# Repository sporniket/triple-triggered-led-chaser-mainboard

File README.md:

# Triple triggered led chaser — Main board

A simple electronic circuit.

Marked as CC0.

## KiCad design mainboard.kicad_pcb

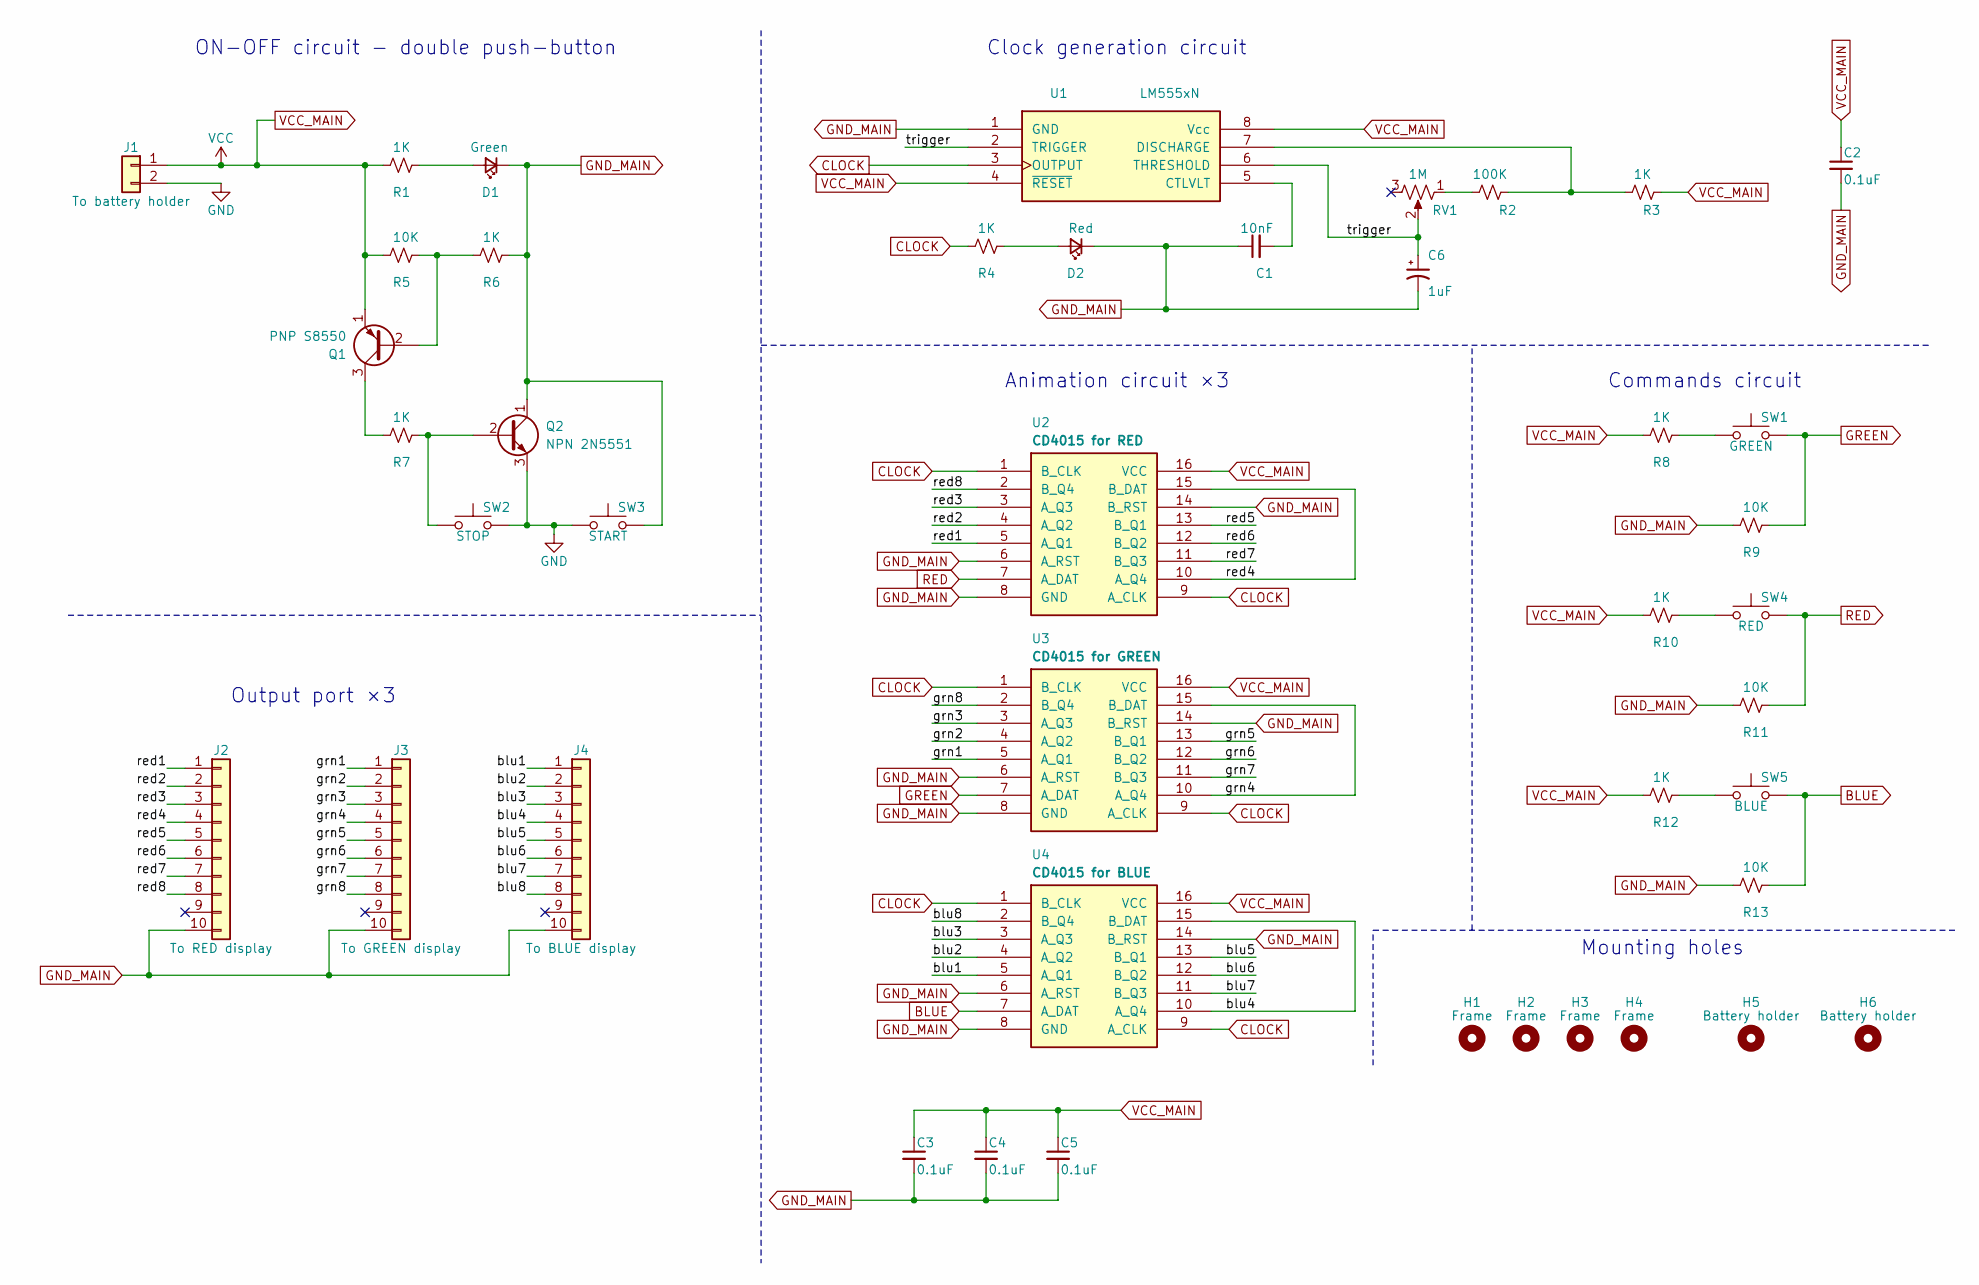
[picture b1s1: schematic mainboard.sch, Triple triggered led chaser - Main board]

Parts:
C1: 10nF; C_Disc_D3.0mm_W1.6mm_P2.50mm
C2, C3, C4, C5: 0.1uF; C_Disc_D3.0mm_W1.6mm_P2.50mm
C6: 1uF; CP_Radial_D4.0mm_P1.50mm
D1: Green; LED_D3.0mm
D2: Red; LED_D3.0mm
H1, H2, H3, H4: Frame; MountingHole_3.2mm_M3_DIN965_Pad
H5, H6: Battery holder; MountingHole_3.2mm_M3_DIN965_Pad
J1: To battery holder; PinHeader_1x02_P2.54mm_Horizontal
J2: To RED display; PinHeader_1x10_P2.54mm_Horizontal
J3: To GREEN display; PinHeader_1x10_P2.54mm_Horizontal
J4: To BLUE display; PinHeader_1x10_P2.54mm_Horizontal
Q1: PNP S8550; TO-92
Q2: NPN 2N5551; TO-92
R1, R3, R4, R6, R7, R8, R10, R12: 1K; R_Axial_DIN0207_L6.3mm_D2.5mm_P10.16mm_Horizontal
R2: 100K; R_Axial_DIN0207_L6.3mm_D2.5mm_P10.16mm_Horizontal
R5, R9, R11, R13: 10K; R_Axial_DIN0207_L6.3mm_D2.5mm_P10.16mm_Horizontal
RV1: 1M; Potentiometer_Piher_PT-6-V_Vertical
SW1: GREEN; SW_PUSH-12mm
SW2: STOP; SW_PUSH-12mm
SW3: START; SW_PUSH-12mm
SW4: RED; SW_PUSH-12mm
SW5: BLUE; SW_PUSH-12mm
U1: LM555xN; DIP-8_W7.62mm
U2: CD4015 for RED; DIP-16_W7.62mm_LongPads
U3: CD4015 for GREEN; DIP-16_W7.62mm_LongPads
U4: CD4015 for BLUE; DIP-16_W7.62mm_LongPads

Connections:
/blu1: J4.1, U4.5 (A_Q1)
/blu2: J4.2, U4.4 (A_Q2)
/blu3: J4.3, U4.3 (A_Q3)
/blu4: J4.4, U4.10 (A_Q4), U4.15 (B_DAT)
/blu5: J4.5, U4.13 (B_Q1)
/blu6: J4.6, U4.12 (B_Q2)
/blu7: J4.7, U4.11 (B_Q3)
/blu8: J4.8, U4.2 (B_Q4)
/grn1: J3.1, U3.5 (A_Q1)
/grn2: J3.2, U3.4 (A_Q2)
/grn3: J3.3, U3.3 (A_Q3)
/grn4: J3.4, U3.10 (A_Q4), U3.15 (B_DAT)
/grn5: J3.5, U3.13 (B_Q1)
/grn6: J3.6, U3.12 (B_Q2)
/grn7: J3.7, U3.11 (B_Q3)
/grn8: J3.8, U3.2 (B_Q4)
/red1: J2.1, U2.5 (A_Q1)
/red2: J2.2, U2.4 (A_Q2)
/red3: J2.3, U2.3 (A_Q3)
/red4: J2.4, U2.10 (A_Q4), U2.15 (B_DAT)
/red5: J2.5, U2.13 (B_Q1)
/red6: J2.6, U2.12 (B_Q2)
/red7: J2.7, U2.11 (B_Q3)
/red8: J2.8, U2.2 (B_Q4)
/trigger: C6.1, RV1.2, U1.2 (TRIGGER), U1.6 (THRESHOLD)
BLUE: R13.1, SW5.2, U4.7 (A_DAT)
CLOCK: R4.2, U1.3 (OUTPUT), U2.1 (B_CLK), U2.9 (A_CLK), U3.1 (B_CLK), U3.9 (A_CLK), U4.1 (B_CLK), U4.9 (A_CLK)
GND: J1.2, Q2.3 (E), SW2.2, SW3.1
GND_MAIN: C1.1, C2.2, C3.2, C4.2, C5.2, C6.2, D1.1 (K), D2.1 (K), J2.10, J3.10, J4.10, Q2.1 (C), R6.1, R9.2, R11.2, R13.2, SW3.2, U1.1 (GND), U2.6 (A_RST), U2.8 (GND), U2.14 (B_RST), U3.6 (A_RST), U3.8 (GND), U3.14 (B_RST), U4.6 (A_RST), U4.8 (GND), U4.14 (B_RST)
GREEN: R9.1, SW1.2, U3.7 (A_DAT)
unnamed: C1.2, U1.5 (CTLVLT)
unnamed: D1.2 (A), R1.1
unnamed: D2.2 (A), R4.1
unnamed: Q1.2 (B), R5.1, R6.2
unnamed: Q1.3 (C), R7.2
unnamed: Q2.2 (B), R7.1, SW2.1
unnamed: R2.1, RV1.1
unnamed: R2.2, R3.1, U1.7 (DISCHARGE)
unnamed: R8.1, SW1.1
unnamed: R10.1, SW4.1
unnamed: R12.1, SW5.1
RED: R11.1, SW4.2, U2.7 (A_DAT)
VCC_MAIN: C2.1, C3.1, C4.1, C5.1, J1.1, Q1.1 (E), R1.2, R3.2, R5.2, R8.2, R10.2, R12.2, U1.4 (~RESET~), U1.8 (Vcc), U2.16 (VCC), U3.16 (VCC), U4.16 (VCC)

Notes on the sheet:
ON-OFF circuit - double push-button
Clock generation circuit
Commands circuit
Animation circuit ×3
Output port ×3
Mounting holes

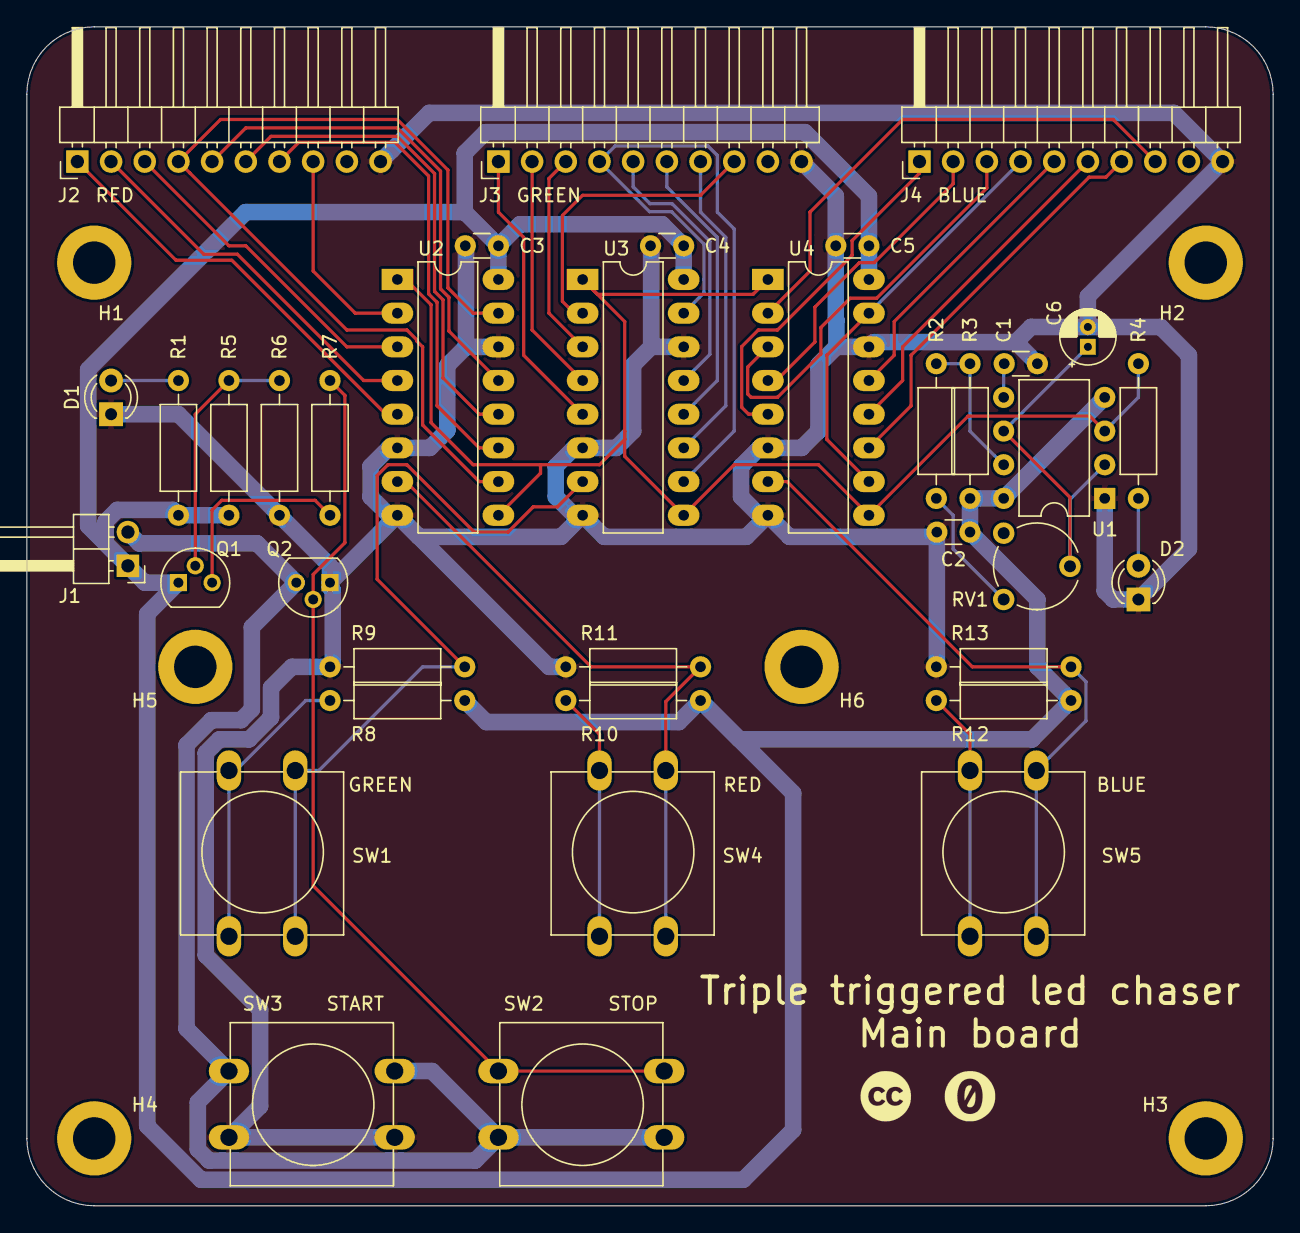
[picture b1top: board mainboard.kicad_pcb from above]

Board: 2 copper layers, 94.0 x 88.9 mm, 43 parts (0 on the bottom side), 43 nets.

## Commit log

2022-03-13 done schematic
2022-03-16 better layout
2022-03-16 applied public repository url to page description
2022-03-16 reset README
2022-03-17 noted actual parts for Q1, Q2 from the prototype
2022-04-02 added bypass capacitors
2022-04-02 assign footprints
2022-04-02 initiate pcb
2022-04-02 added forgotten 1uF capacitor
2022-04-03 fix symbol according to pinout from datasheets
2022-04-03 added mounting holes
2022-04-03 first pcb version
2022-04-03 added datasheets
2022-04-03 update silkscreen, gallery
2022-04-03 adjust J2~J4 labels position
